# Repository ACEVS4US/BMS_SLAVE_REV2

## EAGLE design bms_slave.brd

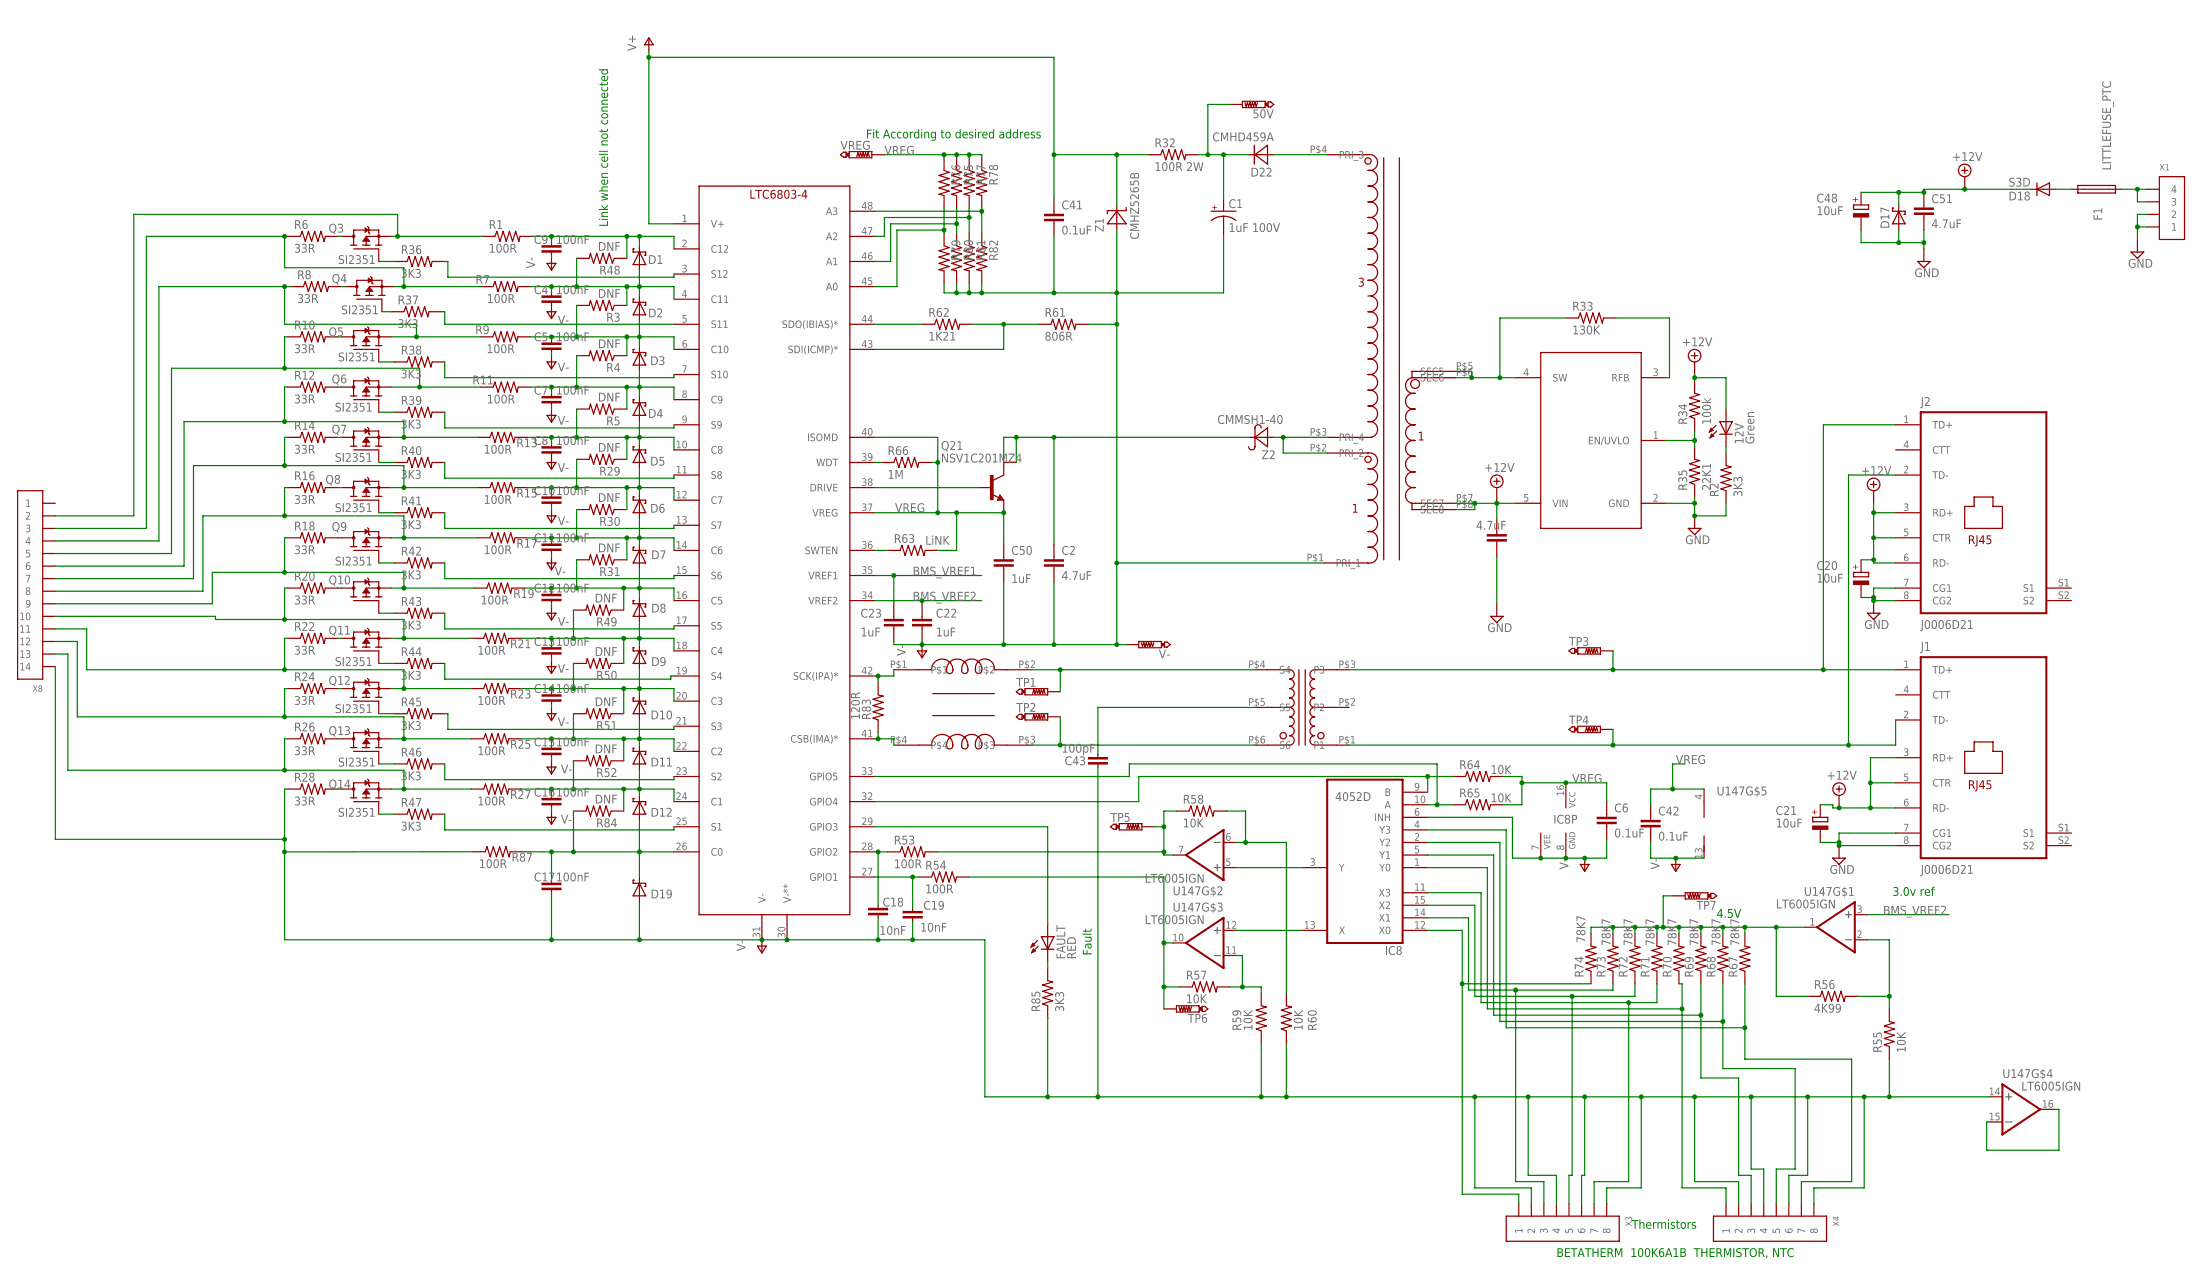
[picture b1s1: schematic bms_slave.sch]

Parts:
12V: Green; CHIP-LED0805
50V: PTR1PAD1-13; P1-13
C1: 1uF 100V; SMC_D
C2, C3, C51: 4.7uF; C1206
C4, C5, C7, C8, C9, C10, C11, C12, C13, C14, C15, C16, C17: 100nF; C0603@1
C6, C41, C42: 0.1uF; C1206
C18, C19: 10nF; C0603@1
C20, C21, C48: 10uF; SMC_D
C22, C23, C50: 1uF; C1206
C43: 100pF; C1206@1
D1, D2, D3, D4, D5, D6, D7, D8, D9, D10, D11, D12, D19: SMF5.0AT1; SOD123FL
D17: SCHOTTKY-DIODESMC; SMC
D18: S3D; SMC
D22: CMHD459A; SOD123
F1: LITTLEFUSE_PTC; 1812
FAULT: RED; CHIP-LED0805
IC8: 4052D; SO16
J1, J2: J0006D21; J0-C/D/E
Q3, Q4, Q5, Q6, Q7, Q8, Q9, Q10, Q11, Q12, Q13, Q14: SI2351; SOT23
Q21: NSV1C201MZ4; SOT223
R1, R7, R9, R11, R13, R15, R17, R19, R21, R23, R25, R27, R53, R54, R87: 100R; R0603
R2, R36, R37, R38, R39, R40, R41, R42, R43, R44, R45, R46, R47, R85: 3K3; R0603
R3, R4, R5, R29, R30, R31, R48, R49, R50, R51, R52, R84: DNF; R0603
R6, R8, R10, R12, R14, R16, R18, R20, R22, R24, R26, R28: 33R; R2512
R32: 100R 2W; R2512
R33: 130K; R0603
R34: 100k; R0603
R35: 22K1; R0603
R55, R57, R58, R59, R60, R64, R65: 10K; R0603
R56: 4K99; R0603
R61: 806R; R0603
R62: 1K21; R0603
R63: LiNK; R0603
R66: 1M; R0603
R67, R68, R69, R70, R71, R72, R73, R74: 78K7; R0603
R75, R76, R77, R78, R79, R80, R81, R82: R-US_R0603; R0603
R83: 120R; R0603
TP1, TP2, TP3, TP4, TP5, TP6, TP7: PTR1PAD1-13; P1-13
U1: LTC6804-2; SSOP48
U21: LT8300; TSOT23-5
U147: LT6005IGN; TSSOP16
U$1: DLW43SH510XK2; DLW43S
U$3: T3001NL
U$15: WURTH_750370040; WE_750370040
V-: PTR1PAD1-13; P1-13
VREG: PTR1PAD1-13; P1-13
X1: CONN_4-1-53261; PB-53261-04
X3, X4: CONN_8-1-53261; PB-53261-08
X8: CONN_14-1-53261; PB-53261-14
Z1: CMHZ5265B; SOD123
Z2: CMMSH1-40; SOD123

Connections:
+12V: 12V.A, C3.1, C20.+, C21.+, C48.+, C51.1, D17.C, D18.C, J1.3 (RD+), J1.5 (CTR), J1.6 (RD-), J2.3 (RD+), J2.5 (CTR), J2.6 (RD-), R34.2, U21.5 (VIN), U$15.P$7 (SEC7), U$15.P$8 (SEC8)
A0: R76.2, R79.1, U1.45 (A0)
A2: R77.2, R81.1, U1.47 (A2)
BMS_VREF1: C23.1, U1.35 (VREF1)
BMS_VREF2: C22.1, U1.34 (VREF2), U147.3 (+IN)
GND: C3.2, C20.-, C21.-, C48.-, C51.2, D17.A, J1.7 (CG1), J1.8 (CG2), J2.7 (CG1), J2.8 (CG2), R2.1, R35.1, U21.2 (GND), X1.1, X1.2
unnamed: Q14.3 (D), R28.2
unnamed: 12V.C, R2.2
unnamed: C4.1, D1.A, D2.C, R3.1, R7.2, R48.2, U1.4 (C11)
unnamed: Q21.1 (B), U1.38 (DRIVE)
unnamed: R37.2, U1.5 (S11)
unnamed: J1.1 (TD+), J2.1 (TD+), TP3.TP, U$3.P$3 (P3)
unnamed: Q13.3 (D), R26.2
unnamed: R45.2, U1.21 (S3)
unnamed: J1.2 (TD-), J2.2 (TD-), TP4.TP, U$3.P$1 (P1)
unnamed: R55.2, R56.2, U147.2 (-IN)
unnamed: R83.2, U1.42 (SCK(IPA)*), U$1.P$1
unnamed: C5.1, D2.A, D3.C, R3.2, R4.1, R9.2, U1.6 (C10)
unnamed: C9.1, D1.C, R1.2, R48.1, U1.2 (C12)
unnamed: Q11.3 (D), R22.2
unnamed: C7.1, D3.A, D4.C, R4.2, R5.1, R11.2, U1.8 (C9)
unnamed: Q10.2 (S), R18.1, R19.1, X8.9
unnamed: FAULT.A, U1.29 (GPIO3)
unnamed: Q3.3 (D), R6.2
unnamed: C8.1, D4.A, D5.C, R5.2, R13.2, R29.1, U1.10 (C8)
unnamed: R46.2, U1.23 (S2)
unnamed: R78.2, R82.1, U1.48 (A3)
unnamed: Q4.3 (D), R8.2
unnamed: C10.1, D5.A, D6.C, R15.2, R29.2, R30.1, U1.12 (C7)
unnamed: FAULT.C, R85.2
unnamed: Q5.3 (D), R10.2
unnamed: C11.1, D6.A, D7.C, R17.2, R30.2, R31.1, U1.14 (C6)
unnamed: C43.1, U$3.P$5 (S5)
unnamed: R36.2, U1.3 (S12)
unnamed: Q6.3 (D), R12.2
unnamed: C12.1, D7.A, D8.C, R19.2, R31.2, R49.1, U1.16 (C5)
unnamed: R38.2, U1.7 (S10)
unnamed: Q7.3 (D), R14.2
unnamed: C13.1, D8.A, D9.C, R21.2, R49.2, R50.1, U1.18 (C4)
unnamed: R39.2, U1.9 (S9)
unnamed: R40.2, U1.11 (S8)
unnamed: Q8.3 (D), R16.2
unnamed: C14.1, D9.A, D10.C, R23.2, R50.2, R51.1, U1.20 (C3)
unnamed: R41.2, U1.13 (S7)
unnamed: R42.2, U1.15 (S6)
unnamed: Q9.3 (D), R18.2
unnamed: C15.1, D10.A, D11.C, R25.2, R51.2, R52.1, U1.22 (C2)
unnamed: Q10.3 (D), R20.2
unnamed: R43.2, U1.17 (S5)
unnamed: D18.A, F1.P$2 (2)
unnamed: C16.1, D11.A, D12.C, R27.2, R52.2, R84.1, U1.24 (C1)
unnamed: R58.2, R60.2, U147.6 (-IN)
unnamed: TP2.TP, U$1.P$3, U$3.P$6 (S6)
unnamed: TP1.TP, U$1.P$2, U$3.P$4 (S4)
unnamed: 50V.TP, C1.+, D22.C, R32.2
unnamed: R75.2, R80.1, U1.46 (A1)
unnamed: F1.P$1 (1), X1.3, X1.4
unnamed: C2.1, Q21.2 (C2), Q21.4 (C4), Z2.C
unnamed: Q4.2 (S), R6.1, R7.1, X8.3
unnamed: Q5.2 (S), R8.1, R9.1, X8.4
unnamed: D22.A, U$15.P$4 (PRI_3)
unnamed: Q9.2 (S), R16.1, R17.1, X8.8
unnamed: Q8.2 (S), R14.1, R15.1, X8.7
unnamed: U$15.P$2 (PRI_2), U$15.P$3 (PRI_4), Z2.A
unnamed: Q11.2 (S), R20.1, R21.1, X8.10
unnamed: Q12.2 (S), R22.1, R23.1, X8.11
unnamed: R33.1, U21.4 (SW), U$15.P$5 (SEC5), U$15.P$6 (SEC6)
unnamed: Q13.2 (S), R24.1, R25.1, X8.12
unnamed: Q14.2 (S), R26.1, R27.1, X8.13
unnamed: R44.2, U1.19 (S4)
unnamed: R33.2, U21.3 (RFB)
unnamed: R34.1, R35.2, U21.1 (EN/UVLO)
unnamed: C17.1, D12.A, D19.C, R84.2, R87.2, U1.26 (C0)
unnamed: Q14.1 (G), R47.1
unnamed: Q13.1 (G), R46.1
unnamed: Q12.1 (G), R45.1
unnamed: Q11.1 (G), R44.1
unnamed: Q10.1 (G), R43.1
unnamed: Q9.1 (G), R42.1
unnamed: Q8.1 (G), R41.1
unnamed: Q7.1 (G), R40.1
unnamed: Q6.1 (G), R39.1
unnamed: Q5.1 (G), R38.1
unnamed: Q4.1 (G), R37.1
unnamed: Q3.2 (S), R1.1, X8.2
unnamed: Q3.1 (G), R36.1
unnamed: R83.1, U1.41 (CSB(IMA)*), U$1.P$4
unnamed: IC8.3 (Y), U147.5 (+IN)
unnamed: R53.2, R58.1, TP5.TP, U147.7 (OUT)
unnamed: R54.2, R57.1, TP6.TP, U147.10 (OUT)
unnamed: IC8.13 (X), U147.12 (+IN)
unnamed: C19.1, R54.1, U1.27 (GPIO1)
unnamed: C18.1, R53.1, U1.28 (GPIO2)
unnamed: IC8.9 (B), R64.1, U1.32 (GPIO4)
unnamed: IC8.10 (A), R65.1, U1.33 (GPIO5)
unnamed: R57.2, R59.2, U147.11 (-IN)
unnamed: R62.1, U1.44 (SDO(IBIAS)*)
unnamed: R61.1, R62.2, U1.43 (SDI(ICMP)*)
unnamed: R63.1, U1.36 (SWTEN)
unnamed: R66.1, U1.39 (WDT)
unnamed: Q6.2 (S), R10.1, R11.1, X8.5
unnamed: Q7.2 (S), R12.1, R13.1, X8.6
unnamed: U147.15 (-IN), U147.16 (OUT)
unnamed: R56.1, R67.2, R68.2, R69.2, R70.2, R71.2, R72.2, R73.2, R74.2, TP7.TP, U147.1 (OUT)
unnamed: IC8.12 (X0), R74.1, X3.1
unnamed: IC8.14 (X1), R73.1, X3.3
unnamed: IC8.15 (X2), R72.1, X3.5
unnamed: IC8.11 (X3), R71.1, X3.7
unnamed: IC8.1 (Y0), R70.1, X4.1
unnamed: IC8.5 (Y1), R69.1, X4.3
unnamed: IC8.2 (Y2), R68.1, X4.5
unnamed: IC8.4 (Y3), R67.1, X4.7
unnamed: R47.2, U1.25 (S1)
Q12: Q12.3 (D), R24.2
V+: C41.1, R32.1, U1.1 (V+), Z1.C
V-: C1.-, C2.2, C4.2, C5.2, C6.2, C7.2, C8.2, C9.2, C10.2, C11.2, C12.2, C13.2, C14.2, C15.2, C16.2, C17.2, C18.2, C19.2, C22.2, C23.2, C41.2, C42.2, C43.2, C50.2, D19.A, IC8.6 (INH), IC8.7 (VEE), IC8.8 (GND), R28.1, R55.1, R59.1, R60.1, R61.2, R79.2, R80.2, R81.2, R82.2, R85.1, R87.1, U1.30 (V-**), U1.31 (V-), U147.13 (V-), U147.14 (+IN), U$15.P$1 (PRI_1), V-.TP, X3.2, X3.4, X3.6, X3.8, X4.2, X4.4, X4.6, X4.8, X8.14, Z1.A
VREG: C6.1, C42.1, C50.1, IC8.16 (VCC), Q21.3 (E), R63.2, R64.2, R65.2, R66.2, R75.1, R76.1, R77.1, R78.1, U1.37 (VREG), U1.40 (ISOMD), U147.4 (V+), VREG.TP

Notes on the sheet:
Thermistors
BETATHERM 100K6A1B THERMISTOR, NTC
Link when cell not connected
3.0v ref
Fit According to desired address
Fault
4.5V

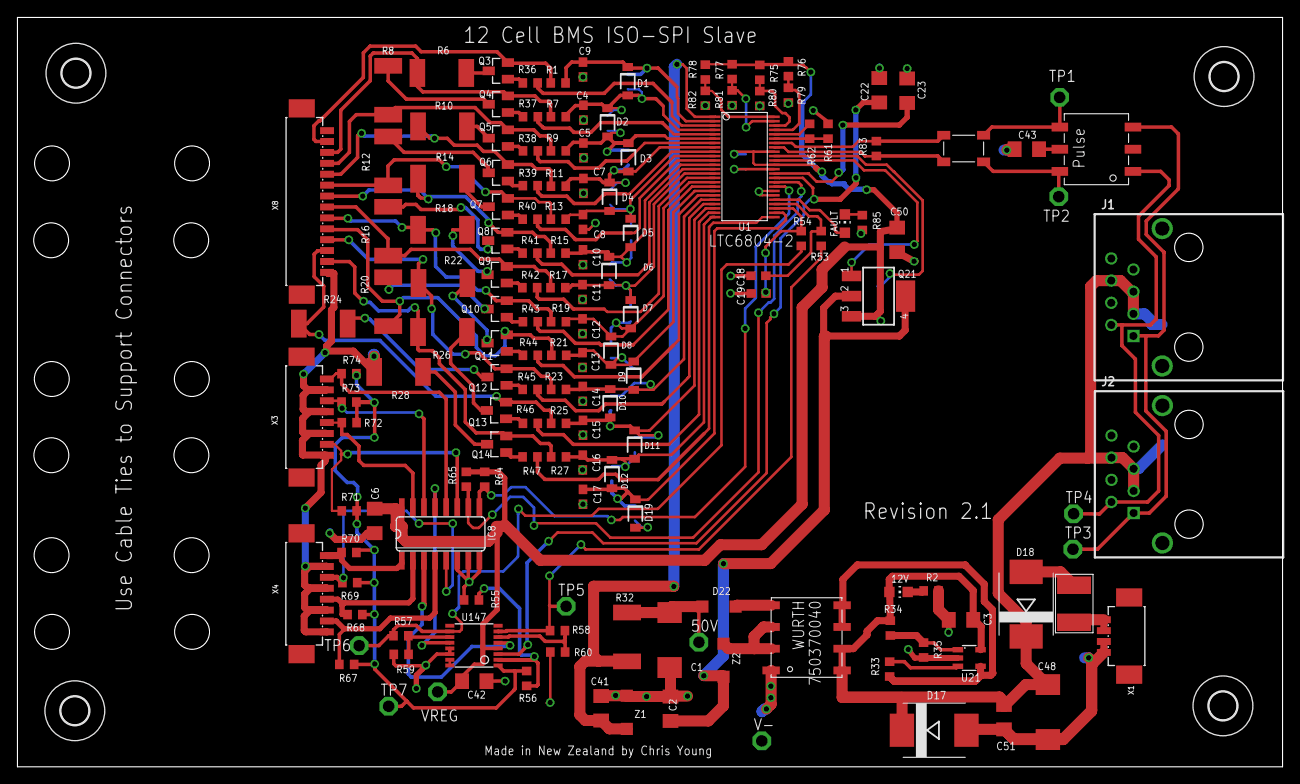
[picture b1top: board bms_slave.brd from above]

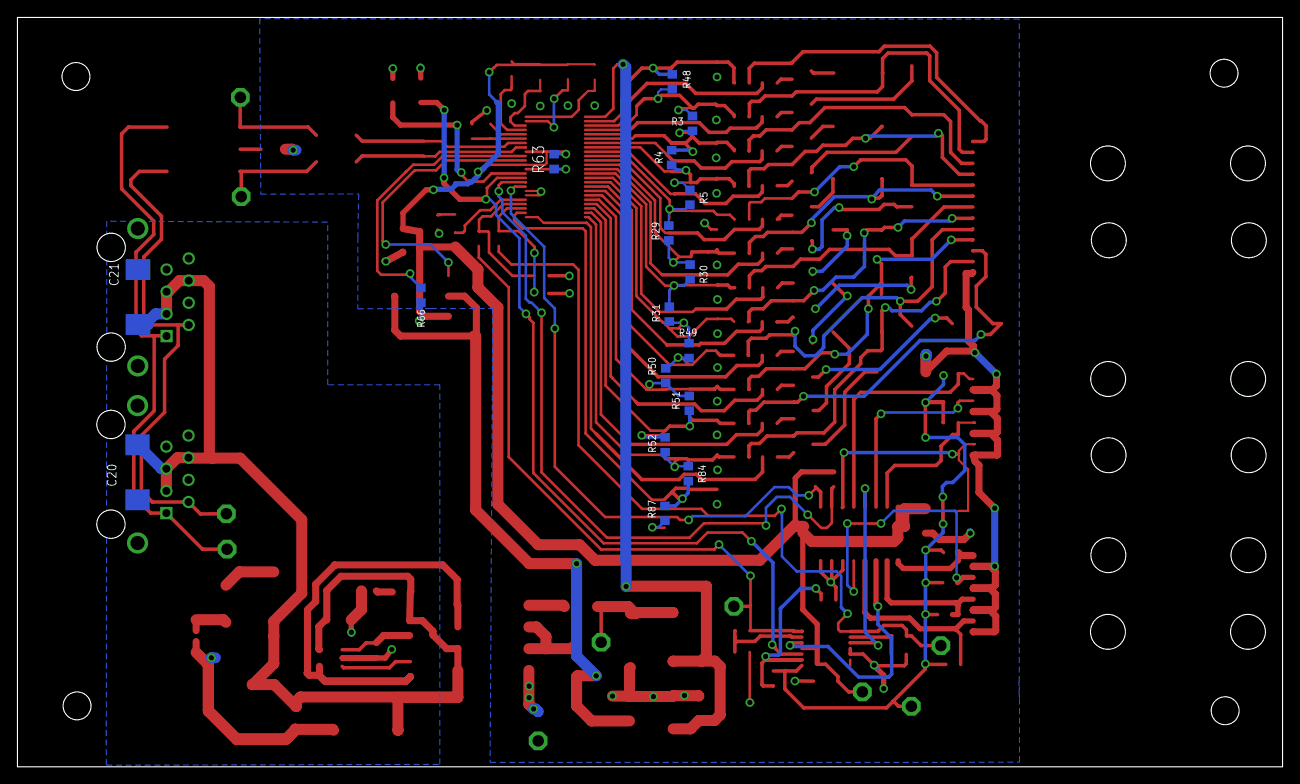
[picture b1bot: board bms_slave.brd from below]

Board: 2 copper layers, 145.0 x 85.9 mm, 176 parts (17 on the bottom side), 117 nets.

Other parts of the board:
H1, H2, H3, H4: MOUNT-HOLE3.2; 3,2

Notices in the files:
parts and their libraries:
pulse-eng: Copyright (C) 2008, Bob Starr
